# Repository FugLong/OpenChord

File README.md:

# OpenChord

A family of open hardware instruments for harmony and music-making. MIT licensed. **OpenChord M Core** (plugin) is free; the **OpenChord M1** box is what we sell.

**M-series** is MIDI. **S-series** is studio. Numbers are generations.

| Product | What it is | Status |
|---------|------------|--------|
| **[OpenChord M1](m1/)** | MIDI-only chord brain. RP2040 hardware under $100, plus free **OpenChord M Core** (AU/VST3, same engine). | Active — engine / proto / plugin v0 |
| **[OpenChord S1](s1/)** | Studio / portable jambox: synth, tracks, the original dream device. | Later |
| M2 / S2 | Next generations of each line. | Not started |

```
OPENCHORD          OPENCHORD
    m1                 s1
```

## Repo layout

```
m1/                     M1 engine, firmware, plugin, hardware, docs (start here)
s1/                     Reserved for the jambox when it is real
archive/s1-daisy/       Frozen Daisy Seed prototype (do not treat as S1)
LICENSE                 MIT
```

The Daisy Seed project that used to live at the repo root is intact under [`archive/s1-daisy/`](archive/s1-daisy/). It is a prototype archive, not the S1 codebase.

## Start with M1

Read [`m1/docs/goals.md`](m1/docs/goals.md) for the product plan (hardware + free plugin). Hands-on testing is [`m1/proto-rp2040`](m1/proto-rp2040/) (RP2040-Zero USB MIDI, **Pro** mode). Plugin: [`m1/plugin`](m1/plugin/) (**OpenChord M Core**, Pro + Smart). The archived Seed box is parked. Do not edit the archive.

## License

MIT — see [LICENSE](LICENSE).

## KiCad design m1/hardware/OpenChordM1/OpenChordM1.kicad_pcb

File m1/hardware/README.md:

# M1 hardware

RP2040 on our PCB, USB-C on the edge. Not a Pico carrier. **Hand-assemble only.** One board, no harnesses.

| Doc | What |
|-----|------|
| [bom.md](bom.md) | Parts + DigiKey/LCSC |
| [support.md](support.md) | Flash / clock / power / USB / MIDI recipe (place before wiring) |
| [switches.md](switches.md) | Gateron LP, direct GPIO (no matrix) |
| [touch.md](touch.md) | Cap strip + trackpad (**IQS572** + **QT2120**) |
| [lib/OLED.md](lib/OLED.md) | OLED pinout / STEP / symbol |
| [lib/TOUCH_ICS.md](lib/TOUCH_ICS.md) | IQS572 + QT2120 EasyEDA/LCSC imports |
| [lib/USB.md](lib/USB.md) | Hroparts TYPE-C-31-M-12 USB-C |
| [lib/TRS.md](lib/TRS.md) | Same Sky SJ1-3523N TRS MIDI |
| [lib/BTN.md](lib/BTN.md) | Panasonic EVQPUC02K edge |
| [lib/MIDI.md](lib/MIDI.md) | Toshiba TLP2361 MIDI IN opto |

Product locks: [`../docs/goals.md`](../docs/goals.md).

## Plan (short)

- **8× Gateron LP** chord pads (hotswap) — mechanical, **one GPIO each** (internal pull-ups; no diodes).
- **IQS572BLQNR** trackpad (color stick XY) + **AT42QT2120** strip only.
- **3× EVQPUC02K** system buttons → GPIO (**roles TBD**). Not capacitive.
- **BOOTSEL** = top tact **TS-1187A** → QSPI_SS through **1 kΩ**, plus **10 kΩ** SS→3V3. No RUN button on rev A.
- Shared **I2C1** on GPIO10/11 (OLED `0x3C`, QT2120 `0x1C`, IQS572 `0x74`; RDY GPIO8, NRST GPIO9). Alps stick = **fallback only**. Pin map: [`support.md`](support.md).
- No SoftPot, no pots, no paid PCBA. Coupon before a later product fab — see [`touch.md`](touch.md).

## Rev A fab (ordering)

| | |
|--|--|
| Size | **118.95 × 63.15 mm** |
| Stack | 4-layer, 1.6 mm, 1 oz. In1 **GND**, In2 **+3.3V**. SMT on **B.Cu**. |
| Finish | **HASL** (not ENIG). Touch = soldermask over copper. |
| Gerbers | [`fab/jlcpcb/`](fab/jlcpcb/) — zip `fab/OpenChordM1-gerbers.zip` (gitignored). Upload that zip. |
| Stencil | **Bottom only**, frameless, custom **160 × 120 mm**, 0.12 mm. No top stencil (`F_Paste` is empty). |
| TRS | SJ1-3523N bushings hang **off** Edge.Cuts so the barrel does not clip FR4. |

## KiCad `lib/`

| Path | Contents |
|------|----------|
| `oled.*` | OLED symbol + footprint + STEP ([OLED.md](lib/OLED.md)) |
| `gateron.*` | Gateron LP hotswap ([GATERON.md](lib/GATERON.md)) |
| `easyeda/oc_touch.*` | IQS572 + QT2120 ([TOUCH_ICS.md](lib/TOUCH_ICS.md)) |
| `easyeda/oc_usb.*` | TYPE-C-31-M-12 USB-C ([USB.md](lib/USB.md)); GCT kept in lib |
| `easyeda/oc_trs.*` | Same Sky SJ1-3523N ([TRS.md](lib/TRS.md)) |
| `easyeda/oc_btn.*` | EVQPUC02K edge + TS-1187A BOOT/RUN ([BTN.md](lib/BTN.md)) |
| `easyeda/oc_midi.*` | Toshiba TLP2361 ([MIDI.md](lib/MIDI.md)) |
| `captouch.*` | Generated electrodes (slider/trackpad) — plugin writes here, not into `OpenChordM1/` |
| `lcsc.*` | Alps stick C219778 (**fallback**) |
| `3dshapes/` | OLED STEP |

Nicknames: `oc-oled`, `oc-lcsc`, `oc-gateron`, `oc-touch`, `oc-usb`, `oc-trs`, `oc-btn`, `oc-midi`, `captouch`. RP2040 = KiCad stock `MCU_RaspberryPi` + `Package_DFN_QFN`. Place slider as `captouch:CT_Slider`. Support ICs (flash **W25Q32JVSSIQ** / [C179173](https://www.lcsc.com/product-detail/C179173.html), LDO/ESD/crystal/diode) = KiCad stock — see [`support.md`](support.md).

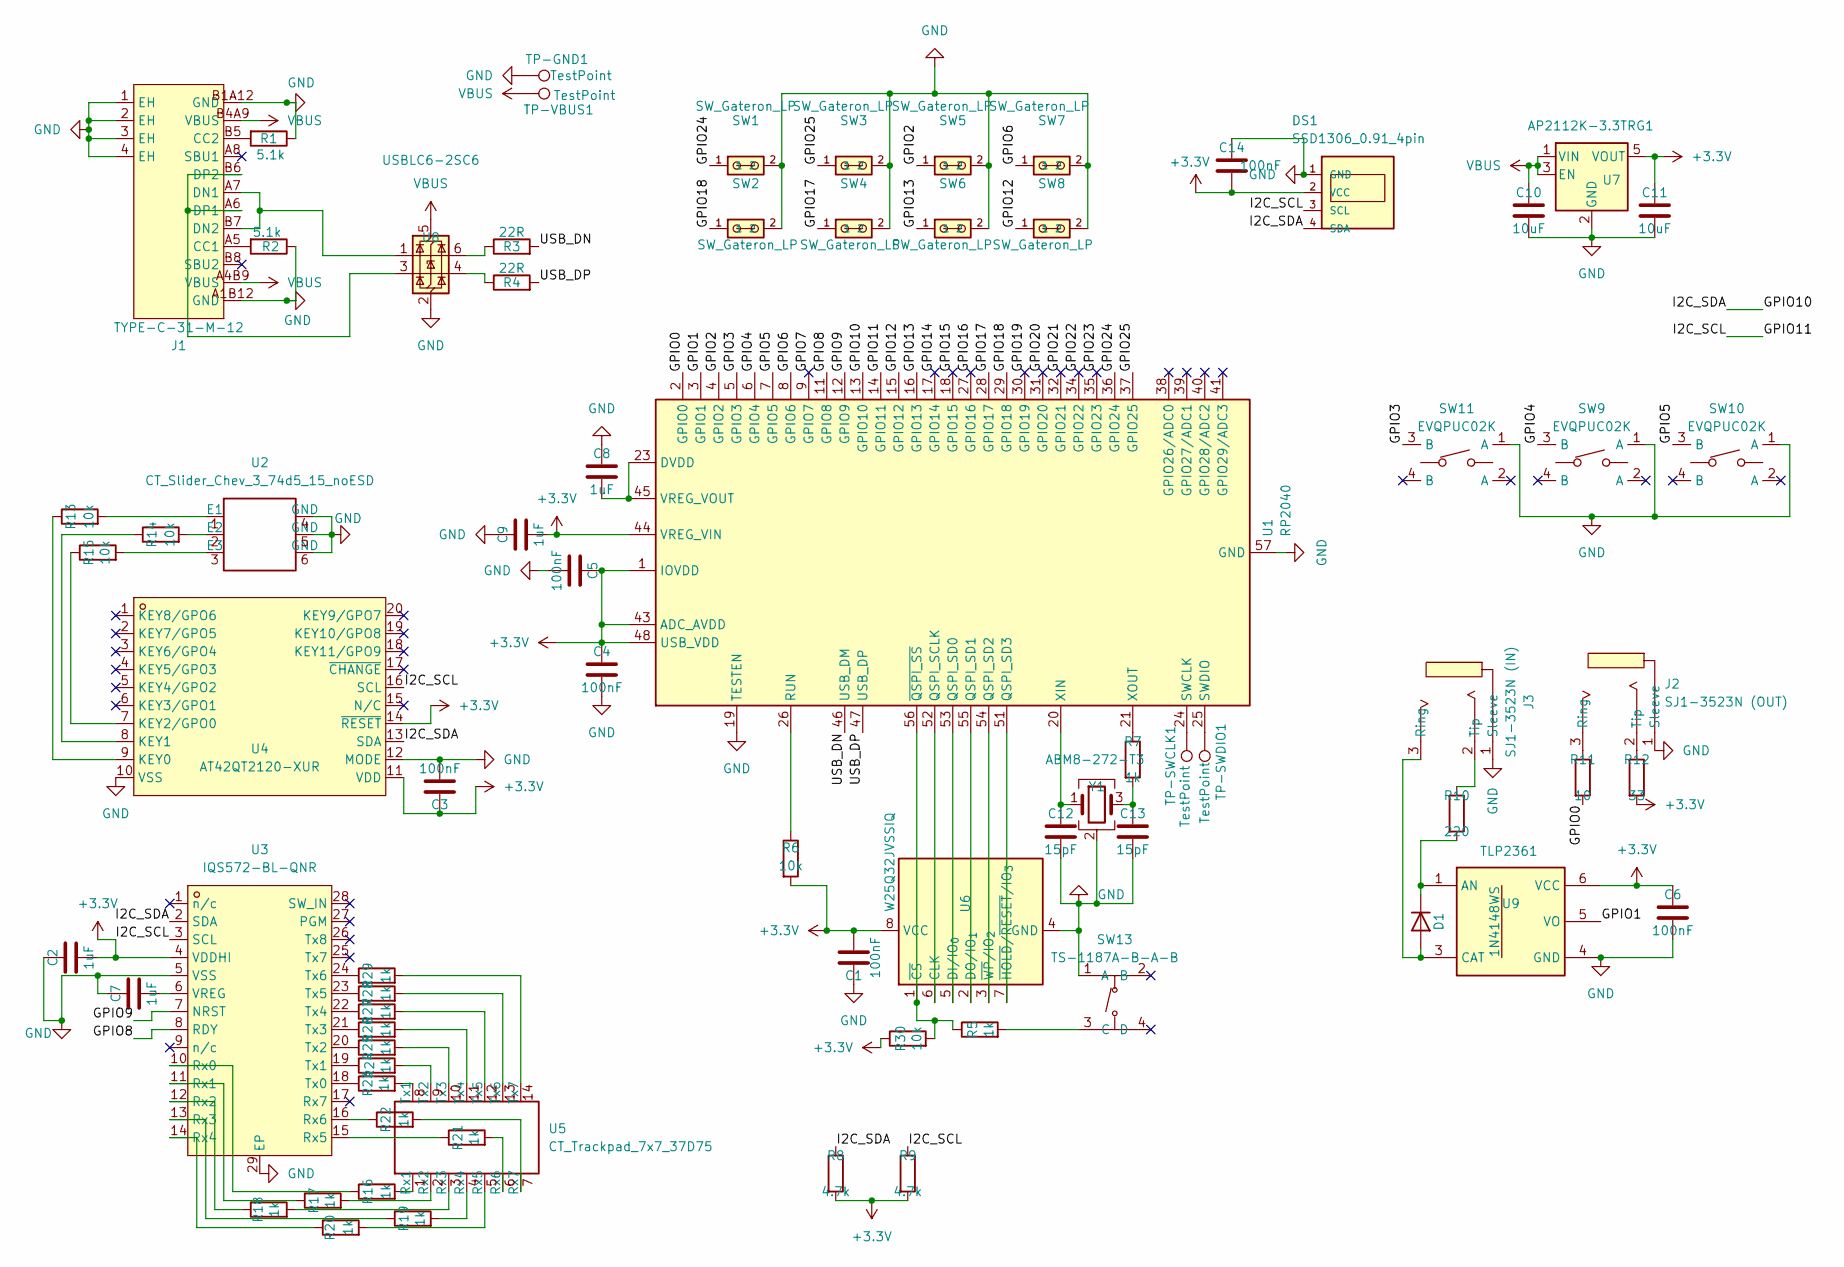
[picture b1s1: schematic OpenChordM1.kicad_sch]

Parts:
C1, C3, C4, C5, C6, C14: 100nF; C_0603_1608Metric; MPN CC0603KRX7R9BB104; LCSC Part C14663
C2, C7, C8, C9: 1uF; C_0603_1608Metric; MPN CC0603KRX5R8BB105; LCSC Part C14664
C10, C11: 10uF; C_0805_2012Metric; MPN CL21A106KOQNNNE; LCSC Part C1713
C12, C13: 15pF; C_0603_1608Metric; MPN CL10C150JB8NNNC; LCSC Part C1644
D1: 1N4148WS; D_SOD-323; MPN 1N4148WS; LCSC Part C2128
DS1: SSD1306_0.91_4pin; SSD1306-0.91-OLED-4pin-128x32; MPN SSD1306 0.91in 4-pin
J1: TYPE-C-31-M-12; MPN TYPE-C-31-M-12; LCSC Part C165948
J2: SJ1-3523N (OUT); SJ1-3523N; MPN SJ1-3523N; LCSC Part C20182914
J3: SJ1-3523N (IN); SJ1-3523N; MPN SJ1-3523N; LCSC Part C20182914
R1, R2: 5.1k; R_0603_1608Metric; MPN 0603WAF5101T5E; LCSC Part C23186
R3, R4: 22R; R_0603_1608Metric; MPN 0603WAF220JT5E; LCSC Part C23345
R5, R7, R16, R17, R18, R19, R20, R21, R22, R23, R24, R25, R26, R27, R28, R29: 1k; R_0603_1608Metric; MPN 0603WAF1001T5E; LCSC Part C21190
R6, R13, R14, R15, R30: 10k; R_0603_1608Metric; MPN RC0603FR-0710KL; LCSC Part C98220
R8, R9: 4.7k; R_0603_1608Metric; MPN 0603WAF4701T5E; LCSC Part C23162
R10: 220; R_0603_1608Metric; MPN 0603WAF2200T5E; LCSC Part C22962
R11: 10; R_0603_1608Metric; MPN 0603WAF100JT5E; LCSC Part C22859
R12: 33; R_0603_1608Metric; MPN 0603WAF330JT5E; LCSC Part C23140
SW1, SW2, SW3, SW4, SW5, SW6, SW7, SW8: SW_Gateron_LP; Gateron-KS33-Hotswap-1U; MPN KS-33 hotswap socket
SW9, SW10, SW11: EVQPUC02K; MPN EVQPUC02K; LCSC Part C79174
SW13: TS-1187A-B-A-B; MPN TS-1187A-B-A-B; LCSC Part C318884
TP-GND1: TestPoint; TestPoint_Pad_D1.5mm
TP-SWCLK1: TestPoint; TestPoint_Pad_D1.5mm
TP-SWDIO1: TestPoint; TestPoint_Pad_D1.5mm
TP-VBUS1: TestPoint; TestPoint_Pad_D1.5mm
U1: RP2040; QFN-56-1EP_7x7mm_P0.4mm_EP3.2x3.2mm; MPN RP2040; LCSC Part C2040
U2: CT_Slider_Chev_3_74d5_15_noESD
U3: IQS572-BL-QNR; QFN-28_L4.0-W4.0-P0.50-TL; MPN IQS572-BL-QNR; LCSC Part C3827635
U4: AT42QT2120-XUR; TSSOP-20_L6.5-W4.4-P0.65-LS6.4-BL; MPN AT42QT2120-XUR; LCSC Part C1522278
U5: CT_Trackpad_7x7_37D75
U6: W25Q32JVSSIQ; SOIC-8_5.3x5.3mm_P1.27mm; MPN W25Q32JVSSIQ; LCSC Part C179173
U7: AP2112K-3.3TRG1; SOT-23-5; MPN AP2112K-3.3TRG1; LCSC Part C51118
U8: USBLC6-2SC6; SOT-23-6; MPN USBLC6-2SC6; LCSC Part C7519
U9: TLP2361; MPN TLP2361(TPL,E); LCSC Part C107626
Y1: ABM8-272-T3; Crystal_SMD_3225-4Pin_3.2x2.5mm; MPN ABM8-272-T3; LCSC Part C20625731

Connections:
+3.3V: C1.2, C2.2, C3.1, C4.1, C5.1, C6.1, C9.2, C11.1, C14.2, DS1.2 (VCC), R6.2, R8.2, R9.2, R12.2, R30.1, U1.1 (IOVDD), U1.10 (IOVDD), U1.22 (IOVDD), U1.33 (IOVDD), U1.42 (IOVDD), U1.43 (ADC_AVDD), U1.44 (VREG_VIN), U1.48 (USB_VDD), U1.49 (IOVDD), U3.4 (VDDHI), U4.11 (VDD), U4.14 (~RESET), U6.8 (VCC), U7.5 (VOUT), U9.6 (VCC)
/GPIO0: R11.2, U1.2 (GPIO0)
/GPIO1: U1.3 (GPIO1), U9.5 (VO)
/GPIO2: SW5.1, U1.4 (GPIO2)
/GPIO3: SW11.3 (B), U1.5 (GPIO3)
/GPIO4: SW9.3 (B), U1.6 (GPIO4)
/GPIO5: SW10.3 (B), U1.7 (GPIO5)
/GPIO6: SW7.1, U1.8 (GPIO6)
/GPIO7: U1.9 (GPIO7)
/GPIO8: U1.11 (GPIO8), U3.8 (RDY)
/GPIO9: U1.12 (GPIO9), U3.7 (NRST)
/GPIO10: DS1.4 (SDA), R8.1, U1.13 (GPIO10), U3.2 (SDA), U4.13 (SDA)
/GPIO11: DS1.3 (SCL), R9.1, U1.14 (GPIO11), U3.3 (SCL), U4.16 (SCL)
/GPIO12: SW8.1, U1.15 (GPIO12)
/GPIO13: SW6.1, U1.16 (GPIO13)
/GPIO14: U1.17 (GPIO14)
/GPIO15: U1.18 (GPIO15)
/GPIO16: U1.27 (GPIO16)
/GPIO17: SW4.1, U1.28 (GPIO17)
/GPIO18: SW2.1, U1.29 (GPIO18)
/GPIO19: U1.30 (GPIO19)
/GPIO20: U1.31 (GPIO20)
/GPIO21: U1.32 (GPIO21)
/GPIO22: U1.34 (GPIO22)
/GPIO23: U1.35 (GPIO23)
/GPIO24: SW1.1, U1.36 (GPIO24)
/GPIO25: SW3.1, U1.37 (GPIO25)
/USB_DN: R3.2, U1.46 (USB_DM)
/USB_DP: R4.2, U1.47 (USB_DP)
GND: C1.1, C2.1, C3.2, C4.2, C5.2, C6.2, C7.1, C8.1, C9.1, C10.2, C11.2, C12.2, C13.2, C14.1, DS1.1 (GND), J1.1 (EH), J1.2 (EH), J1.3 (EH), J1.4 (EH), J1.A1B12 (GND), J1.B1A12 (GND), J2.1 (Sleeve), J3.1 (Sleeve), R1.1, R2.1, SW1.2, SW2.2, SW3.2, SW4.2, SW5.2, SW6.2, SW7.2, SW8.2, SW9.1 (A), SW10.1 (A), SW11.1 (A), SW13.1 (A), TP-GND1.1 (1_1), U1.19 (TESTEN), U1.57 (GND), U2.4 (GND), U2.5 (GND), U2.6 (GND), U3.5 (VSS), U3.29 (EP), U4.10 (VSS), U4.12 (MODE), U6.4 (GND), U7.2 (GND), U8.2 (GND), U9.4 (GND), Y1.2 (G), Y1.4 (G)
unnamed: C13.1, R7.2, Y1.3
unnamed: D1.2 (A), J3.3 (Ring), U9.3 (CAT)
unnamed: D1.1 (K), R10.2, U9.1 (AN)
unnamed: J1.A5 (CC1), R2.2
unnamed: J1.B5 (CC2), R1.2
unnamed: J1.A7 (DN1), J1.B7 (DN2), U8.1 (I/O1)
unnamed: J1.A6 (DP1), J1.B6 (DP2), U8.3 (I/O2)
unnamed: J2.3 (Ring), R11.1
unnamed: J2.2 (Tip), R12.1
unnamed: J3.2 (Tip), R10.1
unnamed: R3.1, U8.6 (I/O1)
unnamed: R4.1, U8.4 (I/O2)
unnamed: R5.2, SW13.3 (C)
unnamed: U1.52 (QSPI_SCLK), U6.6 (CLK)
unnamed: U1.53 (QSPI_SD0), U6.5 (DI/IO_{0})
unnamed: U1.55 (QSPI_SD1), U6.2 (DO/IO_{1})
unnamed: U1.54 (QSPI_SD2), U6.3 (~WP/IO_{2})
unnamed: U1.51 (QSPI_SD3), U6.7 (~HOLD/~RESET/IO_{3})
unnamed: R6.1, U1.26 (RUN)
unnamed: TP-SWCLK1.1 (1_1), U1.24 (SWCLK)
unnamed: TP-SWDIO1.1 (1_1), U1.25 (SWDIO)
unnamed: C8.2, U1.23 (DVDD), U1.45 (VREG_VOUT), U1.50 (DVDD)
unnamed: C12.1, U1.20 (XIN), Y1.1
unnamed: R7.1, U1.21 (XOUT)
unnamed: R5.1, R30.2, U1.56 (~QSPI_SS), U6.1 (~CS)
unnamed: R13.2, U2.1 (E1)
unnamed: R14.2, U2.2 (E2)
unnamed: R15.2, U2.3 (E3)
unnamed: R16.1, U3.10 (Rx0)
unnamed: R17.1, U3.11 (Rx1)
unnamed: R18.1, U3.12 (Rx2)
unnamed: R19.1, U3.13 (Rx3)
unnamed: R20.1, U3.14 (Rx4)
unnamed: R21.1, U3.15 (Rx5)
unnamed: R22.1, U3.16 (Rx6)
unnamed: R23.1, U3.18 (Tx0)
unnamed: R24.1, U3.19 (Tx1)
unnamed: R25.1, U3.20 (Tx2)
unnamed: R26.1, U3.21 (Tx3)
unnamed: R27.1, U3.22 (Tx4)
unnamed: R28.1, U3.23 (Tx5)
unnamed: R29.1, U3.24 (Tx6)
unnamed: C7.2, U3.6 (VREG)
unnamed: R13.1, U4.9 (KEY0)
unnamed: R14.1, U4.8 (KEY1)
unnamed: R15.1, U4.7 (KEY2/GPO0)
unnamed: R16.2, U5.1 (Rx1)
unnamed: R17.2, U5.2 (Rx2)
unnamed: R18.2, U5.3 (Rx3)
unnamed: R19.2, U5.4 (Rx4)
unnamed: R20.2, U5.5 (Rx5)
unnamed: R21.2, U5.6 (Rx6)
unnamed: R22.2, U5.7 (Rx7)
unnamed: R23.2, U5.8 (Tx1)
unnamed: R24.2, U5.9 (Tx2)
unnamed: R25.2, U5.10 (Tx3)
unnamed: R26.2, U5.11 (Tx4)
unnamed: R27.2, U5.12 (Tx5)
unnamed: R28.2, U5.13 (Tx6)
unnamed: R29.2, U5.14 (Tx7)
VBUS: C10.1, J1.A4B9 (VBUS), J1.B4A9 (VBUS), TP-VBUS1.1 (1_1), U7.1 (VIN), U7.3 (EN), U8.5 (VBUS)

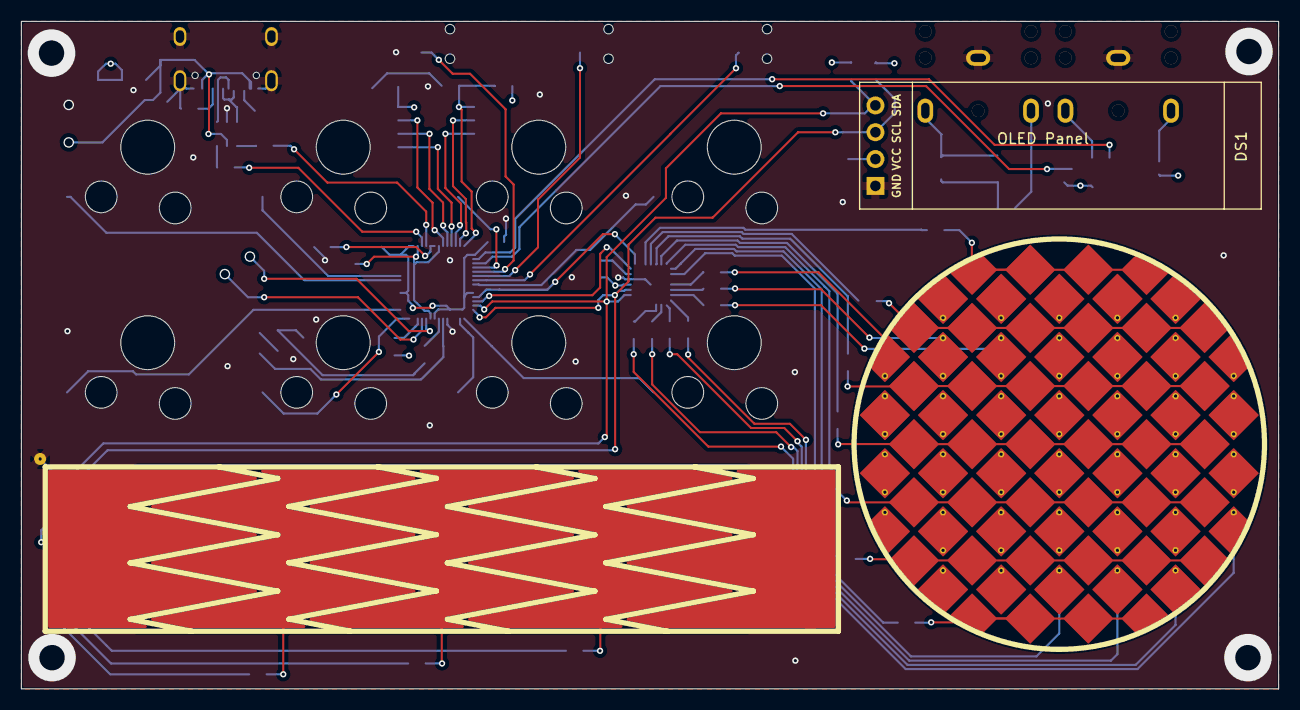
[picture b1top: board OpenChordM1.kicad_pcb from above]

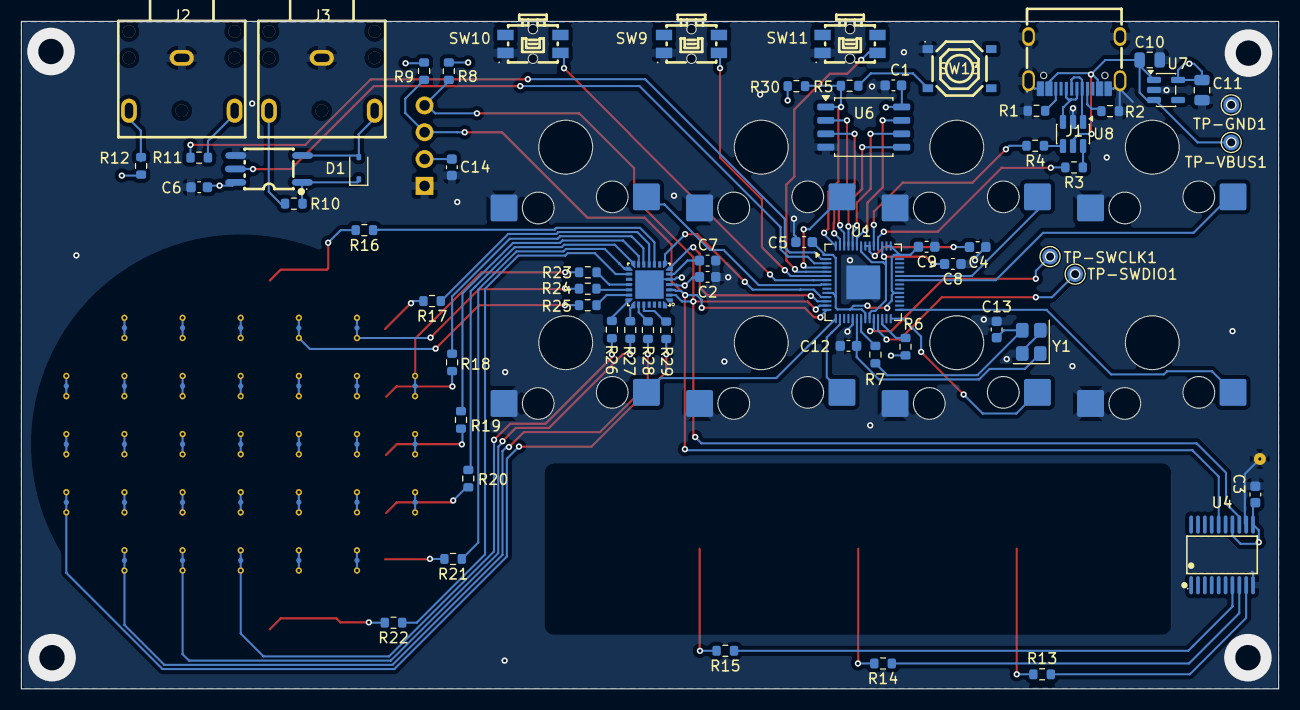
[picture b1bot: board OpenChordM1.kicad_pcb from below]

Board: 4 copper layers, 119.0 x 63.1 mm, 75 parts (72 on the bottom side), 82 nets.

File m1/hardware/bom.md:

# M1 BOM (rev A)

Matches `OpenChordM1/OpenChordM1.kicad_sch`. Wiring: [`support.md`](support.md). Touch: [`touch.md`](touch.md).

**Hand-build.** 0603 unless noted. Electrodes **U2 / U5** and test pads are copper — not buy items.

Prices from carts **2026-09-19**: [LCSC](https://www.lcsc.com/) `$40.78` + [DigiKey](https://www.digikey.com/) `$29.50` = **`$70.28` for 5**. Every schematic electronic is in one of those two carts. Still buy OLED / Gateron / PCB / cover elsewhere.

## Cost

| | **1 unit** | **5 units** |
|--|----------:|----------:|
| LCSC + DigiKey carts (MOQ leftovers in) | 14.06 | **70.28** |
| OLED | 1.20 | 6.00 |
| 8× socket + 8× KS-33 | 3.04 | 15.20 |
| 4-layer PCB + DHL | ~10 | ~50 |
| Printed cover | ~2 | ~10 |
| Cart shipping | ~4 | ~20 |
| **Landed (US, no labor)** | **~$34** | **~$171** |

Not included: assembly, stencil, solder, keycaps, scrap, tariffs. **ENIG** for gold touch pads is extra **~$5–8**/board. Qty ~100 is roughly **$16–20**/unit.

Biggest lines: PCB, IQS **$2.07**, QT **$1.93**, 2× TRS **$1.90**, flash **$1.49**, OLED **$1.20**, RP2040 **$1.00**.

---

## ICs

| Qty | Ref | Part | MPN | Pkg | $ | Buy |
|----:|-----|------|-----|-----|--:|-----|
| 1 | U1 | MCU | RP2040 | QFN-56 7×7 | 1.00 | [LCSC C2040](https://www.lcsc.com/product-detail/C2040.html) |
| 1 | U6 | Flash 32 Mbit | W25Q32JVSSIQ | SOIC-8 208 mil | 1.49 | [LCSC C179173](https://www.lcsc.com/product-detail/C179173.html) |
| 1 | Y1 | 12 MHz | ABM8-272-T3 | 3.2×2.5 | 0.63 | [LCSC C20625731](https://www.lcsc.com/product-detail/C20625731.html) |
| 1 | U7 | 3.3 V LDO | AP2112K-3.3TRG1 | SOT-23-5 | 0.17 | [LCSC C51118](https://www.lcsc.com/product-detail/C51118.html) |
| 1 | U8 | USB ESD | USBLC6-2SC6 | SOT-23-6 | 0.18 | [LCSC C7519](https://www.lcsc.com/product-detail/C7519.html) |
| 1 | U3 | Trackpad | IQS572BLQNR | QFN-28 4×4 | 2.07 | [DigiKey](https://www.digikey.com/en/products/detail/azoteq-pty-ltd/IQ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 (KiCad `IQS572-BL-QNR`) |
| 1 | U4 | Cap strip | AT42QT2120-XUR | TSSOP-20 | 1.93 | [DigiKey](https://www.digikey.com/en/products/detail/microchip-technol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 |
| 1 | U9 | MIDI IN opto | TLP2361(TPL,E) | SO6 | 0.53 | [LCSC C107626](https://www.lcsc.com/product-detail/C107626.html) |
| 1 | D1 | MIDI IN clamp | 1N4148WS | SOD-323 | 0.02 | [LCSC C2128](https://www.lcsc.com/product-detail/C2128.html) |
| | | | | | **8.02** | |

Do not buy leftover **W25Q16JV** / C131025. Flash cart qty is **10** (MOQ).

## Connectors & buttons

| Qty | Ref | Part | MPN | Pkg | $ | Buy |
|----:|-----|------|-----|-----|--:|-----|
| 1 | J1 | USB-C | TYPE-C-31-M-12 | SMT+TH | 0.17 | [LCSC C165948](https://www.lcsc.com/product-detail/C165948.html) |
| 2 | J2 OUT, J3 IN | TRS 3.5 mm | SJ1-3523N | TH R/A | 1.90 | [DigiKey](https://www.digikey.com/en/products/detail/same-sky-formerly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 |
| 3 | SW9–SW11 | System | EVQPUC02K | SMD side + bosses | 0.53 | [LCSC C79174](https://www.lcsc.com/product-detail/C79174.html) |
| 1 | SW13 | BOOTSEL | TS-1187A-B-A-B | SMD 5.1×5.1 | 0.02 | [LCSC C318884](https://www.lcsc.com/product-detail/C318884.html) |
| | | | | | **2.62** | |

No RUN button on rev A.

## Display, switches, sockets

Not in the LCSC/DigiKey carts.

| Qty | Ref | Part | $ | Buy |
|----:|-----|------|--:|-----|
| 1 | DS1 | OLED 0.91" white SSD1306 4-pin | 1.20 | [AliExpress](https://www.aliexpress.com/w/wholesale-0.91-oled-ssd1306-128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 |
| 8 | SW1–SW8 | LP hotswap socket (KS-27 / KS-33) | 1.25 | [Gateron](https://www.gateron.com/products/gateron-low-profile-switch-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 · [beekeeb](https://shop.beekeeb.com/products/gateron-low-profile-hotswa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 |
| 8 | — | KS-33 (KS-27 OK) | 1.79 | [Gateron 35-pack](https://www.gateron.com/products/gateron-ks-33-low-profile-s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 |
| | | | **4.24** | |

Sockets are on the schematic; switches plug in after fab. Five boards need **40** sockets and **40** switches (two 35-packs). OLED pinout GND / VCC / SCL / SDA — [`lib/OLED.md`](lib/OLED.md).

## Passives

In the LCSC cart. Equivalents OK if value + package match. Crystal load caps stay **C0G**. 10 µF is **0805**; everything else **0603**.

| /board | Cart | Value | Refs | Use | $ | LCSC |
|-------:|-----:|-------|------|-----|--:|------|
| 2 | 100 | 22 Ω | R3, R4 | USB D+/D− | 0.00 | [C23345](https://www.lcsc.com/product-detail/C23345.html) |
| 2 | 100 | 5.1 kΩ | R1, R2 | USB-C CC → GND | 0.00 | [C23186](https://www.lcsc.com/product-detail/C23186.html) |
| 16 | 200 | 1 kΩ | R5, R7, R16–R29 | BOOTSEL, XOUT, IQS Tx/Rx | 0.05 | [C21190](https://www.lcsc.com/product-detail/C21190.html) |
| 5 | 100 | 10 kΩ | R6, R13–R15, R30 | RUN PU, QT SNS, QSPI_SS PU | 0.02 | [C98220](https://www.lcsc.com/product-detail/C98220.html) |
| 2 | 100 | 4.7 kΩ | R8, R9 | I2C1 pull-ups | 0.01 | [C23162](https://www.lcsc.com/product-detail/C23162.html) |
| 1 | 100 | 220 Ω | R10 | MIDI IN LED | 0.01 | [C22962](https://www.lcsc.com/product-detail/C22962.html) |
| 1 | 100 | 10 Ω | R11 | MIDI OUT TX → Ring | 0.00 | [C22859](https://www.lcsc.com/product-detail/C22859.html) |
| 1 | 100 | 33 Ω | R12 | MIDI OUT 3V3 → Tip | 0.00 | [C23140](https://www.lcsc.com/product-detail/C23140.html) |
| 6 | 100 | 100 nF | C1, C3–C6, C14 | decoupling | 0.08 | [C14663](https://www.lcsc.com/product-detail/C14663.html) |
| 4 | 100 | 1 µF | C2, C7–C9 | IQS VDDHI/VREG, RP2040 VREG | 0.06 | [C14664](https://www.lcsc.com/product-detail/C14664.html) |
| 2 | 50 | 15 pF C0G | C12, C13 | crystal load | 0.02 | [C1644](https://www.lcsc.com/product-detail/C1644.html) |
| 2 | 40 | 10 µF 0805 | C10, C11 | LDO in / out | 0.13 | [C1713](https://www.lcsc.com/product-detail/C1713.html) |
| | | | | **Consumed / board** | **0.38** | |
| | | | | **Bags / board** (cart ÷ 5) | **1.72** | |

## PCB + cover

**118.95 × 63.15 mm**, 4-layer, HASL. [JLCPCB](https://jlcpcb.com/) — **~$10**/board at qty 5. Cover **~$2** filament.

---

## Orders (5 boards)

Re-import these CSVs (vendor export format, quantities for 5 boards):

- LCSC: [`carts/OpenChordM1-LCSC-qty5.csv`](carts/OpenChordM1-LCSC-qty5.csv)
- DigiKey: [`carts/OpenChordM1-DigiKey-qty5.csv`](carts/OpenChordM1-DigiKey-qty5.csv)

1. **LCSC `$40.78`** — 22 lines: C2040, C179173 (qty 10), C165948, C51118, C7519, C20625731, C107626, C2128, C79174 (qty 15), C318884 (qty 20), plus the 12 passives above.
2. **DigiKey `$29.50`** — [IQS572BLQNR](https://www.digikey.com/en/products/detail/azoteq-pty-ltd/IQ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 ×5, [AT42QT2120-XUR](https://www.digikey.com/en/products/detail/microchip-technol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 ×5, [SJ1-3523N](https://www.digikey.com/en/products/detail/same-sky-formerly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 ×10.
3. 5× OLED; **40** Gateron LP sockets + **40** KS-33 (two 35-packs).
4. JLCPCB 4-layer, ~119 × 63 mm, qty 5.

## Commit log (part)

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2025-07-31 initial commit, docs, starter code
2025-07-31 Readme update
2025-07-31 Doc cleanup
2025-07-31 Readme refinement
2025-08-01 pinout image test fix
2025-08-01 pinout theme fix (hopefully)
2025-08-01 pinout image fix v3
2025-08-04 finished V1 of the parts list
2025-08-04 Update readmes to reflect new parts list doc
2025-08-04 added back to main docs button on docs
2025-08-13 Partslist fixes, readme update
2025-08-13 Fixed incorrect cap listings
2025-08-25 added basic voice + volume + midi support
2025-08-25 Update readme to reflect updates
2025-08-28 major refactor, single tone w/ volume
2025-08-28 added midi support back in, piano mode now
2025-08-28 readme cleanup
2025-09-04 Fixed optocoupler requirements, using midi hub properly
2025-12-18 Got TRS midi in working!
    Back on my grind
2025-12-20 Add TRS MIDI improvements, SD card support, and bugfixes
2025-12-20 Midi trs optimizations
2025-12-21 Moved to external usb, SD card updates
2025-12-21 disable debug mode
2025-12-21 SD card usb flash drive scripts, audio tests
2025-12-21 battery monitoring added
2025-12-21 Screen SPI init
2025-12-21 screen init and broken test
2025-12-22 fixed button matrix, got screen working, input manager
    Also I FUCKING BROKE BOTH SHITTY ASS 20 DOLLAR SCREENS I HAD. NOW I HAVE TO REDO THE WHOLE TOP OF THE ENCLOSURE AND REWIRE EVERYTHING. AND of course I have to buy 2 more screens just hoping I won't b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
2025-12-30 Hardware integration done!! Debug UI added
    Now firmware dev really begins
2025-12-30 Chord mapping plugin built out, initial UI
2025-12-30 main UI manager started
2025-12-31 UX refinement, bugfixes
2025-12-31 drum pad, bug fixes, bin file handling
2025-12-31 pitch bend, mod wheel, UI cleanup
2025-12-31 Optimization, cleanup, battery monitor tweaks
2026-01-01 Midi transport, global settings, UX tweaks, bugfixes
2026-01-01 Note mode refactor + updates, chord mode rename, UX tweaks
2026-01-02 Battery tweaks, major settings refactor
2026-01-02 battery charging, something else I forgot.
    sleepy
2026-01-03 UX improvements, first instrument and fx
    I broke usb midi :(
2026-01-04 Big main cleanup/refactor
2026-01-04 Fixed midi, we goated
2026-01-04 Added more FX plugins, UI scrollbar
2026-01-04 encoder improvements
2026-01-04 Synth audio fixes, clarity better now
